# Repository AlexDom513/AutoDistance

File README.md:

# autoDistance
The goal of this project is to implement a simple [PID controller](https://en.wikipedia.org/wiki/Proportional%E2%80%93integral%E2%80%93derivative_controller) using a FPGA. [(1)](https://www.youtube.com/watch?v=JFTJ2SS4xyA) and [(2)](https://www.youtube.com/watch?v=oy58S4beC9c) served as the inspiration for this project. Note that a FPGA is being used as an exercise. It is much more convenient to use a microcontroller for this application.

## PID Algorithm
Before starting to implement the PID controller in hardware, a [Python script](https://github.com/AlexDom513/autoDistance/blob/main/algo-dev/algo2.py) was used to understand the algorithm and the system it would be used in. The script was set up in such a way that the user can specify variables like the set-point, the PID gains, and the cart mass.

A simulation then shows how the cart position is affected by the changing angle of a ramp:

## FPGA Modules
### PulseController
The [PulseController](https://github.com/AlexDom513/autoDistance/blob/main/fpga-source/source/PulseController.vhd) module is responsible for interacting with the ultrasonic sensor. According to the [datasheet](https://github.com/AlexDom513/autoDistance/blob/main/datasheets/HCSR04.pdf), the FPGA must send a 10 microsecond trigger pulse. The sensor the sends eight 40 kHz pulses and detects whether there is a returned pulse. If there is a returned pulse, the time of high output from the sensor is proportional to the distance detected.

### PIDController
After obtaining the cart distance in the PulseController module, the [PIDController](https://github.com/AlexDom513/autoDistance/blob/main/fpga-source/source/PidController.vhd) module is used to compute an appropriate ramp angle so that the cart will be directed towards the ramp's center. Proportional gain (P) is a function of where the cart is located along the ramp. Integral gain (I) continues to increase while the cart's observed position is different from the target position. Derivative gain (D) is dependent on how quickly the cart is approaching the target position. A state machine is used to jump between states that contain different computations (error, gains, ramp angle, scaling/saturation).

### StepperController
Whenever a new ramp angle is computed, it is passed to the [StepperController](https://github.com/AlexDom513/autoDistance/blob/main/fpga-source/source/StepperController.vhd) module. This module translates the value into physical movement by the stepper motor attached to the ramp. Two state machines are used to implement this functionality (Stepper State Machine & Pulse State Machine). The Stepper State Machine has a counter that is used to track the position of the stepper motor. The counter is set to 0 during startup. We then monitor whether the output from PIDController is greater than or less than the current value of the counter. Depending on the condition, we will either have the stepper motor increment or decrement from its current position. A signal that controls the motor's direction is set low/high and the Pulse State Machine is used to send trigger pulses to a [A4988](https://components101.com/modules/a4988-stepper-motor-driver-module) motor controller. The stepper motor finally increments or decrements in the desired direction.

## Circuit Schematics
Note: toggled controlled signals (via switches) are NOT shown

### Sensor Circuit
Converts the +3.3V Trig_Pulse signal to +5V logic. Signal is connected to ultrasonic sensor (HC-SR04). The sensor outputs a +5V signal which is converted back to +3.3V before being passed to the FPGA.

### Stepper Circuit
Connects control signals (Step_Pulse, Dir_Sel) from the FPGA to the stepper control board (A4988). Since the design is using 1/8 microstepping, MS1 and MS2 are also tied to +5V.

## CAD
This was my first serious attempt at creating a 3D model! All parts were printed using PLA on a PRUSA MK3.

[My Parts](https://cad.onshape.com/documents/018887aac5e3fe98b3ecc4ac/w/28ee8de5f592833dfd0388a2/e/8ab51c28ebdef6fccae7c0ab?renderMode=1&uiState=657551bd4254d404bca63ac2) |
[HC-SR04 Model](https://grabcad.com/library/hcsr04-ultrasonic-sensor-1) |
[NEMA-17 Model](https://grabcad.com/library/nema17-42-40-1) |
[Motor Bracket](https://grabcad.com/library/nema-17-stepper-motor-mounting-bracket-2)

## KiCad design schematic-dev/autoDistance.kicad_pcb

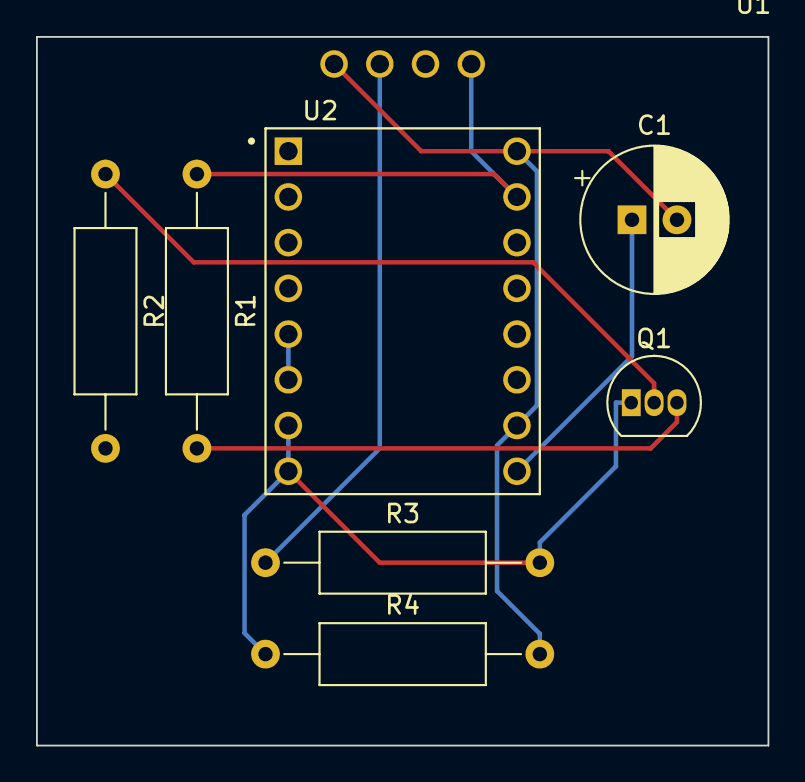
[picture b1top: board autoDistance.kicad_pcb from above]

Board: 2 copper layers, 40.6 x 39.4 mm, 8 parts (0 on the bottom side), 8 nets.

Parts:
C1: 100 uF; CP_Radial_D8.0mm_P2.50mm
Q1: PN2222A; TO-92_Inline
R1: 5K; R_Axial_DIN0309_L9.0mm_D3.2mm_P15.24mm_Horizontal
R2: 2K; R_Axial_DIN0309_L9.0mm_D3.2mm_P15.24mm_Horizontal
R3: 1K; R_Axial_DIN0309_L9.0mm_D3.2mm_P15.24mm_Horizontal
R4: 1.88K; R_Axial_DIN0309_L9.0mm_D3.2mm_P15.24mm_Horizontal
U1: HC-SR04; XCVR_HC-SR04
U2: A4988_STEPPER_MOTOR_DRIVER_CARRIER; MODULE_A4988_STEPPER_MOTOR_DRIVER_CARRIER

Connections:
+5V: R1.1, U1.1 (VCC), U2.15 (VDD)
+12V: C1.1, U2.9 (VMOT)
ARTY: Q1.1 (E), R3.2, R4.1, U2.7 (STEP), U2.8 (DIR)
GND: C1.2, R4.2, U1.4 (GND), U2.10 (GND), U2.16 (GND)
unnamed: Q1.2 (B), R2.1
unnamed: Q1.3 (C), R1.2, U1.2 (TRIG)
unnamed: R3.1, U1.3 (ECHO)
unnamed: U2.5 (~RESET), U2.6 (~SLEEP)

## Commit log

2023-09-25 file-reorg + algo prototype start
2023-09-28 sim progress
2023-09-29 sim improvements + pid tuning
2023-09-29 added schematic capture
2023-10-14 mechanical
2023-10-23 mechDev + sim work
2023-10-28 reorganization
2023-10-28 simulation updates
2023-11-01 sim improvements using GHDL and GTKwave
2023-11-03 added PAUSE state + makefile improvements
2023-11-04 ultrasonic functional
2023-11-04 add top-level module, update makefile
2023-11-05 add stepper coupler
2023-11-08 revamp mechanical design
2023-11-13 StepperController Start
2023-11-14 Stepper Controller compiles
2023-11-15 Sim Start
2023-11-18 bugfix
2023-11-19 StepperController tested on hardware
2023-11-21 fixed point math start
2023-11-24 math update for pulseController, now sends proper distance
2023-11-25 pid module progress
2023-11-26 progress towards proportional gain implementation
2023-12-02 proportional control, partially working
2023-12-04 proportional system working on hardware
2023-12-04 noise analysis
2023-12-10 Core functionality achieved
2023-12-10 project cleanup
2023-12-10 markdown
2023-12-18 SMA filter
2023-12-18 microstep fix
2023-12-27 schematic updates
2024-01-01 tuning + deadzone + fixes
2024-01-01 add pic
